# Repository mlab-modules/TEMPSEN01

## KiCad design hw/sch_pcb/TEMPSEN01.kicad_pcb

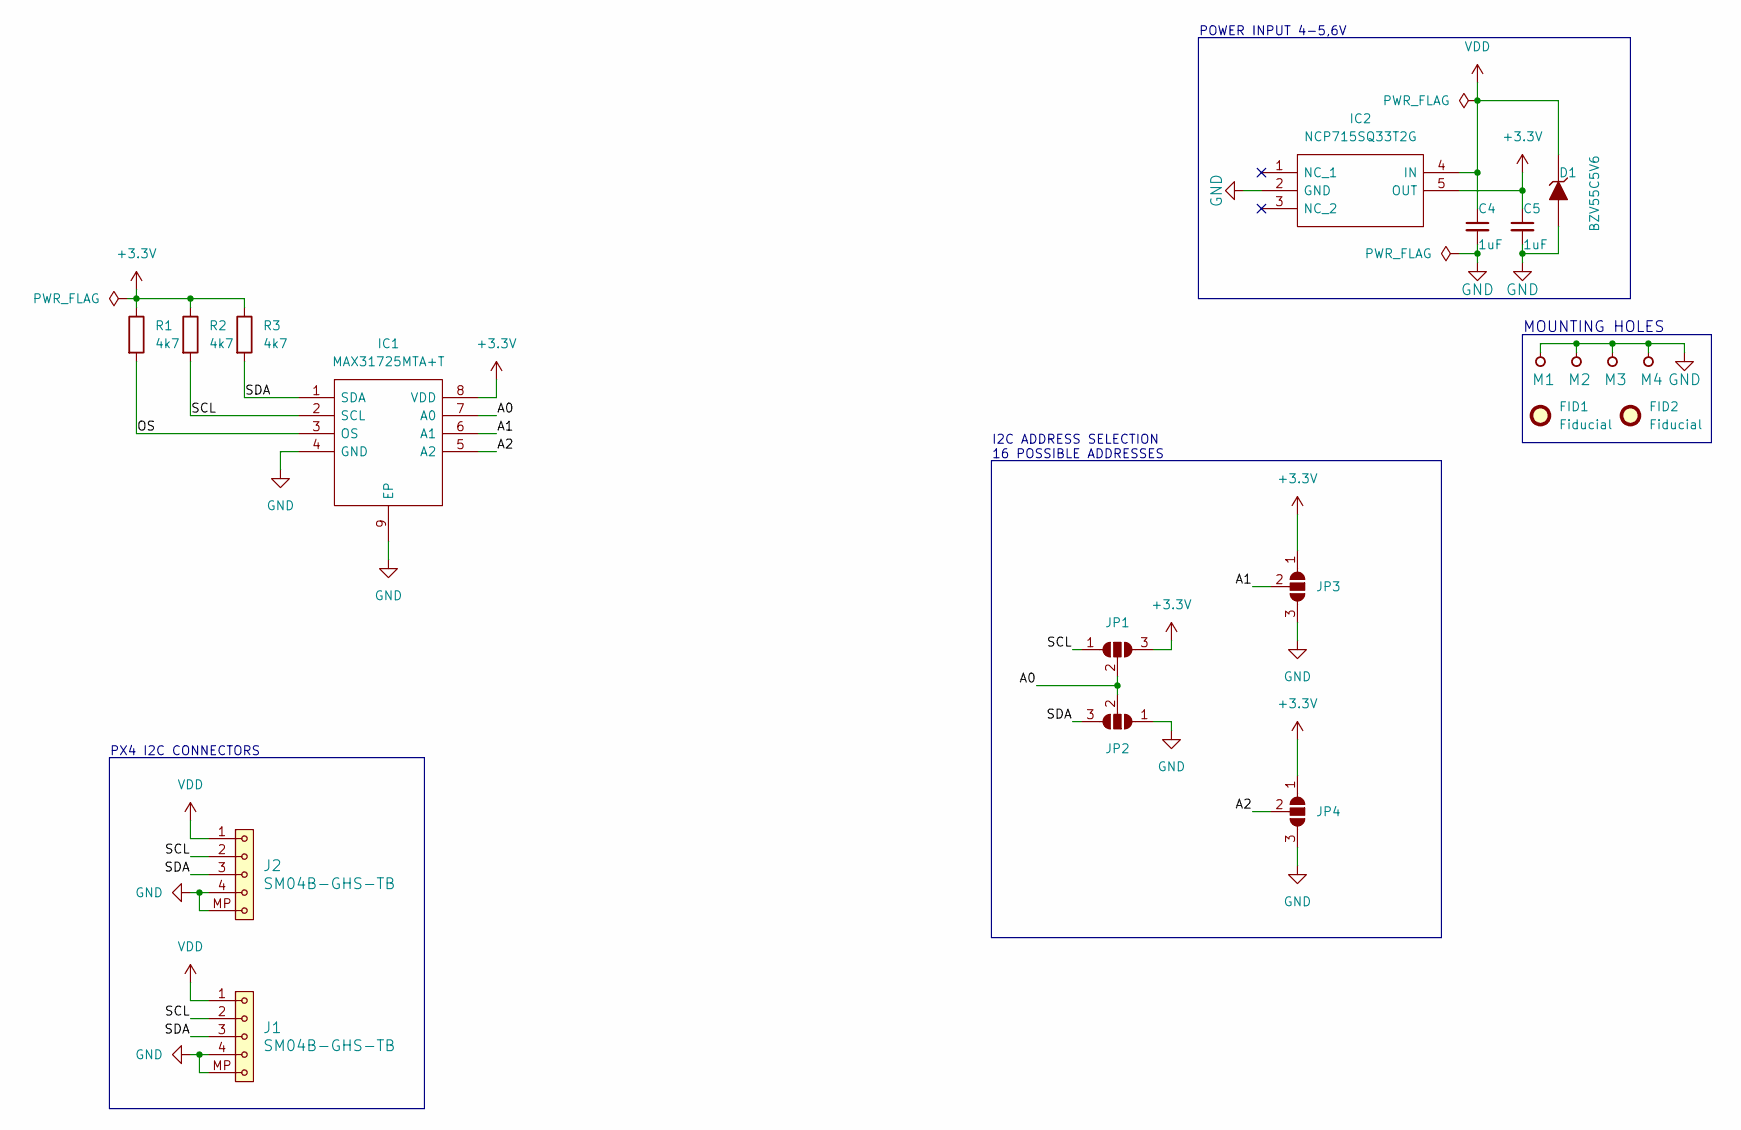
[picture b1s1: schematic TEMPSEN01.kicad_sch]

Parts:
C4, C5: 1uF; C_0805_2012Metric_Pad1.18x1.45mm_HandSolder
D1: BZV55C5V6; D_SOD-123F
FID1, FID2: Fiducial; Fiducial_1mm_Mask2mm
IC1: MAX31725MTA+T; SON65P300X300X80-9N; Mouser Part Number 700-MAX31725MTA+T
IC2: NCP715SQ33T2G; SOT65P210X110-5N; Mouser Part Number 863-NCP715SQ33T2G
J1, J2: SM04B-GHS-TB; JST_GH_SM04B-GHS-TB_1x04-1MP_P1.25mm_Horizontal
JP1, JP2, JP3, JP4: SolderJumper_3_Open; SolderJumper-3_P1.3mm_Open_RoundedPad1.0x1.5mm
M1, M2, M3, M4: HOLE; MountingHole_3mm
R1, R2, R3: 4k7; R_0805_2012Metric_Pad1.20x1.40mm_HandSolder

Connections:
+3.3V: C5.1, IC1.8 (VDD), IC2.5 (OUT), JP1.3 (B), JP3.1 (A), JP4.1 (A), R1.1, R2.1, R3.1
/A0: IC1.7 (A0), JP1.2 (C), JP2.2 (C)
/A1: IC1.6 (A1), JP3.2 (C)
/A2: IC1.5 (A2), JP4.2 (C)
/OS: IC1.3 (OS), R1.2
/SCL: IC1.2 (SCL), J1.2, J2.2, JP1.1 (A), R2.2
/SDA: IC1.1 (SDA), J1.3, J2.3, JP2.3 (B), R3.2
GND: C4.2, C5.2, D1.2 (A), IC1.4 (GND), IC1.9 (EP), IC2.2 (GND), J1.4, J1.MP, J2.4, J2.MP, JP2.1 (A), JP3.3 (B), JP4.3 (B), M1.1, M2.1, M3.1, M4.1
VDD: C4.1, D1.1 (K), IC2.4 (IN), J1.1, J2.1

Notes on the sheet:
POWER INPUT 4-5,6V
I2C ADDRESS SELECTION 16 POSSIBLE ADDRESSES
PX4 I2C CONNECTORS
MOUNTING HOLES

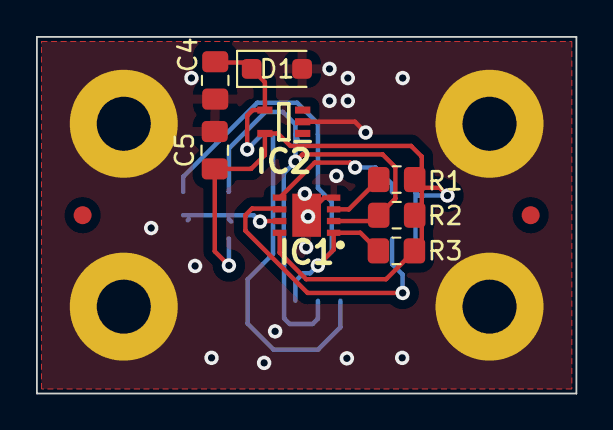
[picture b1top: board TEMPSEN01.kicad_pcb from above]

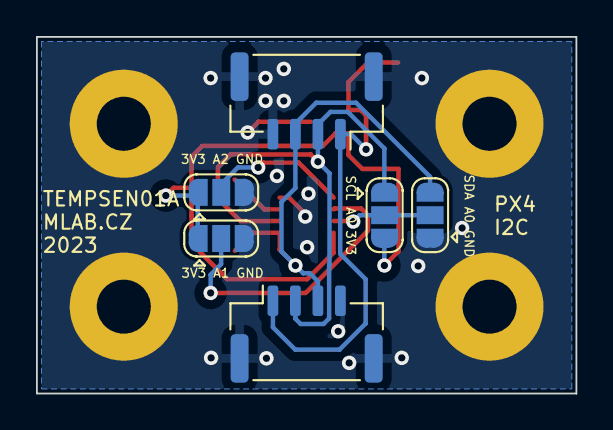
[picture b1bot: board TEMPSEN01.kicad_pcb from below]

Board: 2 copper layers, 30.0 x 19.8 mm, 20 parts (6 on the bottom side), 9 nets.

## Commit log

2023-09-22 Update metadata files
2023-09-22 schematics and pcb drawing
2023-09-23 Update workflow files
2023-09-23 Update actions products
